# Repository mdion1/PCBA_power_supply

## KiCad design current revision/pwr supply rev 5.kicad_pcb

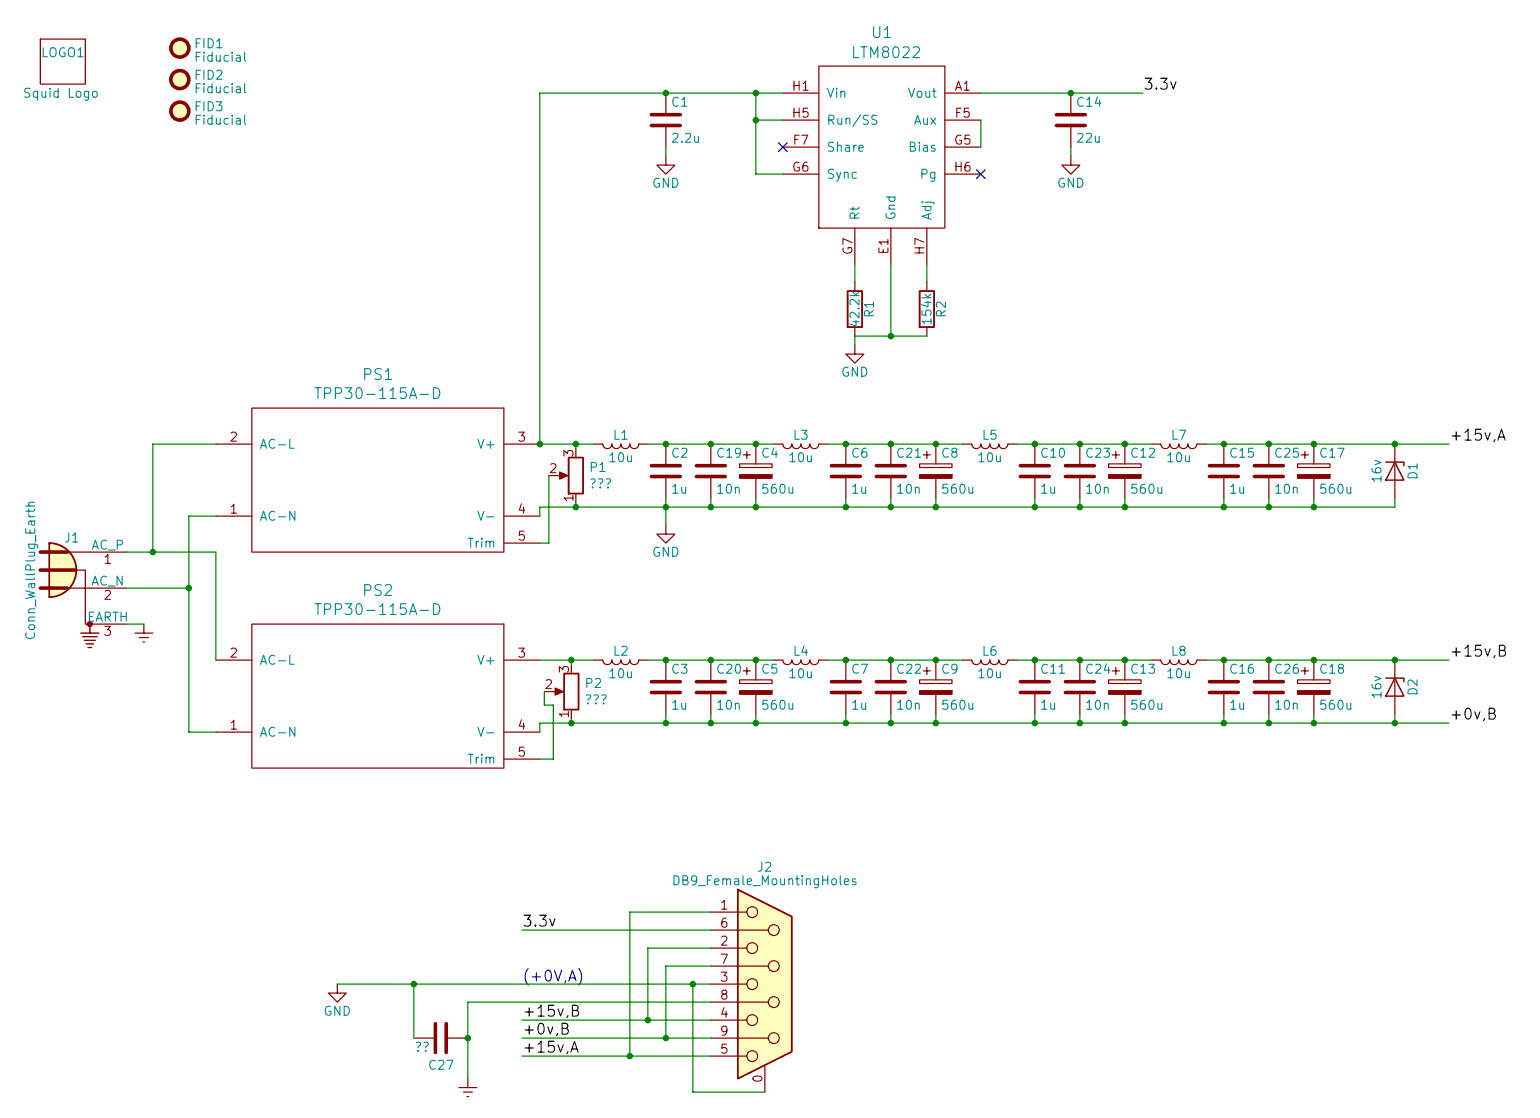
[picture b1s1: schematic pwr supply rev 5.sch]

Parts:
C1: 2.2u; C_0603_1608Metric; MPN C1608JB1E225M080AB
C2, C3, C6, C7, C10, C11, C15, C16: 1u; C_0603_1608Metric; MPN GRT188R61H105ME13D
C4, C5, C8, C9, C12, C13, C17, C18: 560u; CP_Radial_D10.0mm_P5.00mm; MPN EEU-FR1V561
C14: 22u; C_0805_2012Metric; MPN GRM219R61C226ME15KL
C19, C20, C21, C22, C23, C24, C25, C26: 10n; C_0603_1608Metric; MPN '885012206089
C27: ??; C_Disc_D3.0mm_W1.6mm_P2.50mm
D1, D2: 16v; D_DO-201_P5.08mm_Vertical_KathodeUp; MPN TP1.5KE18A
FID1, FID2, FID3: Fiducial; Fiducial_0.75mm_Mask1.5mm
J1: Conn_WallPlug_Earth; PF0030PC; MPN PF0030/PC
J2: DB9_Female_MountingHoles; DB9FC_w_housing_connection; MPN ID09S33E4GX00LF
L1, L2, L3, L4, L5, L6, L7, L8: 10u; 6045_inductor; MPN ASPI-6045S-100MT
LOGO1: Squid Logo; SquidLogo20x24
P1, P2: ???; Potentiometer_Trimmer_Bourns_3296W
PS1, PS2: TPP30-115A-D; TPP-30-115A-D; MPN TPP-30-115A-D
R1: 42.2k; R_0603_1608Metric; MPN ERA-3AEB4222V
R2: 154k; R_0603_1608Metric; MPN RT0603BRD07154KL
U1: LTM8022; LGA-50; MPN LTM8022EV#PBF

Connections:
/3.3v: C14.1, J2.6, U1.A1 (Vout)
/+0v,B: C3.2, C5.2, C7.2, C9.2, C11.2, C13.2, C16.2, C18.2, C20.2, C22.2, C24.2, C26.2, D2.2 (A), J2.7, J2.9, P2.1, PS2.4 (V-)
/+15v,A: C15.1, C17.1, C25.1, D1.1 (K), J2.1, J2.5, L7.1
/+15v,B: C16.1, C18.1, C26.1, D2.1 (K), J2.2, J2.4, L8.1
Earth: C27.1, J1.3 (EARTH), J2.8
GND: C1.2, C2.2, C4.2, C6.2, C8.2, C10.2, C12.2, C14.2, C15.2, C17.2, C19.2, C21.2, C23.2, C25.2, C27.2, D1.2 (A), J2.0 (PAD), J2.3, P1.1, PS1.4 (V-), R1.2, R2.2, U1.E1 (Gnd)
unnamed: C1.1, L1.2, P1.3, PS1.3 (V+), U1.G6 (Sync), U1.H1 (Vin), U1.H5 (Run/SS)
unnamed: C10.1, C12.1, C23.1, L5.1, L7.2
unnamed: C11.1, C13.1, C24.1, L6.1, L8.2
unnamed: C2.1, C4.1, C19.1, L1.1, L3.2
unnamed: C3.1, C5.1, C20.1, L2.1, L4.2
unnamed: C6.1, C8.1, C21.1, L3.1, L5.2
unnamed: C7.1, C9.1, C22.1, L4.1, L6.2
unnamed: J1.1 (AC_P), PS1.2 (AC-L), PS2.2 (AC-L)
unnamed: J1.2 (AC_N), PS1.1 (AC-N), PS2.1 (AC-N)
unnamed: L2.2, P2.3, PS2.3 (V+)
unnamed: P1.2, PS1.5 (Trim)
unnamed: P2.2, PS2.5 (Trim)
unnamed: R1.1, U1.G7 (Rt)
unnamed: R2.1, U1.H7 (Adj)
unnamed: U1.F5 (Aux), U1.G5 (Bias)

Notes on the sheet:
(+0V,A)

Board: 2 copper layers, 50 parts (29 on the bottom side), 21 nets, no tracks yet.

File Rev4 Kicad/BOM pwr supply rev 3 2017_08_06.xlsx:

Id | Designator | Package | Quantity | Designation | Supplier | Supplier P/N | MPN | Alternatives
1 | PS2,PS1 | TPP 30-115A-D | 2 | TPP 30-115A-D | Mouser | 495-TPP30-115A-D |  |  | $35.63/e @ qty 25
2 | C1 | C_0603 | 1 | 2.2u | Mouser | C1608JB1E225M080AB |  | C1608X5R1E225K080AE | $0.113/e @ qty 10
3 | C2,C3,C6,C7,C10,C11,C15,C16 | C_0603 | 8 | 1u | Mouser | 963-GMK107BJ105KAHT |  | CL10A105KB8NNNC, GRT188R61H105ME13D | $0.104/e @ qty 100
4 | C4,C5,C8,C9,C12,C13,C17,C18 | CP_Radial_D10.0mm_P5.00mm | 8 | 560u | Mouser | 667-EEU-FR1V561 |  |  | $0.373/e @ qty 100
5 | C14 | C_0805 | 1 | 22u | Mouser | EMK212BBJ226MG-T |  | GRM219R61C226ME15K | $0.442/e @ qty 10
6 | J2 | DB9FC | 1 | DB9_Female_MountingHoles | Mouser | 649-ID09S33E4GX00LF |  |  | $0.827/e @ qty 10
7 | R1 | R_0603 | 1 | 42.2k | Mouser | ERA-3AEB4222V |  |  | $0.249/e @ qty 10
8 | R2 | R_0603 | 1 | 154k | Mouser | 667-ERA-3AEB1543V |  |  | $0.249/e @ qty 10
9 | J1 | AC_receptacle | 1 | Conn_WallPlug_Earth | Mouser | 562-703W-00/54 |  |  | $0.858/e @ qty 20
10 | C19,C20,C21,C22,C23,C24,C25,C26 | C_0603 | 8 | 10n | Mouser | 710-885012206089 |  | GCM188R72A103KA37D | $0.054/e @ qty 100
11 | U1 | LGA-50 | 1 | LTM8022 | Digikey | LTM8022EV#PBF-ND |  |  | $10.13/e @ qty 25
12 | L1,L2,L3,L4,L5,L6,L7,L8 | 6045_inductor | 8 | 10u | Mouser | 815-ASPI-6045S-100MT |  |  | $0.468/e @ qty 50
13 | D1,D2 | PowerDI5 | 2 | 31v | Mouser | 576-TP1.5KE18A (alt footprint) |  |  | $0.62/e @ qty 10
 |  |  | 43

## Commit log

2021-01-22 Initial commit with previous versions
2021-01-22 Slight modification to rev 5, added cap from local to earth gnd, adjustment pots, silkscreen changes
2021-02-24 initial commit for new layout, smaller board, new AC entry module
